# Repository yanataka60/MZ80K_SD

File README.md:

# MZ-80シリーズにSD-Cardとのロード、セーブ機能を

　ROMをF000Hに置くことでMZ-80シリーズにフロッピーディスク装置を外付けした際に起動するためのFDコマンドを利用できますが、フロッピーディスク装置の代わりにSD-CARDを繋いでしまおうというものです。

#### 　2025.7.31追記 MZ-80K、MZ-80K2、MZ-80K2E、MZ-80C、MZ-1200、MZ-700で動作しますが、MZ-700はRAMとの切替動作をサポートしたMZ-700_SDもあります。

　アダプタを繋ぐだけでもBASIC SP-5030が約4秒で起動できるようになるなどアプリケーションランチャーとして便利に使えますが、MONITOR SP-1002にパッチをあてることでBASIC SP-5030はもちろん、ほとんどのMZ-80KアプリケーションがSD-CARD対応となります。

### 本体ROMをパッチを当てたMONITOR SP-1002に交換しなくてもアプリケーションからのロード、セーブをSD対応とさせるパッチあてWindows用ツール「CMT2SD_CHECK」を公開しました。(2022.6.29)
### 詳細は、CMT2SD_CHECKフォルダ中のREADME.mdを参照してください。

　MZ-700もMZ-80K用アプリケーションについては同様にSD-CARD対応となりますが、標準添付のS-BASIC、Hu-BASICともMONITOR 1Z-009A、1Z-009BのCMTルーチンを利用していないためMONITOR 1Z-009A、1Z-009BにパッチをあてただけではSD-CARD対応となりません。

　S-BASICについてはパッチを当てることでSD-CARD対応となりますが、Hu-BASICは未対応です。

　基本的にはMZ-700ではMZ-80K互換機として利用できると考えてください。

　また、MZ-700もFDxコマンドは機能しますのでMZ-700用アプリケーションランチャーとして使えますが、MZ-80K対応とうたっていない64KオールRAMを前提としているMZ-700用アプリケーションはロードできない可能性があります。

　MZ-700+MZ-80K_SDでMZ-700用アプリケーションを実行したときにMZ-80K_SDのROMとMZ-700本体のRAMが衝突しないよう「ROM切り離しスイッチ」を取り入れましたが、これを自動で行うMZ-700_SD基板も公開しています。ただし、MZ-700_SDを作成するにはGAL16V8の入手が必要です。

　なお、一部のMZ-80K用ソフトはMZ-700で実行するにあたって、0h!MZ別冊 ADVANCED MZ-700に掲載されているSP-1002のMZ-700対応版 NZ-700が必要となるものがあります。

https://github.com/yanataka60/MZ-700_SD

#### 注）

　一応安定動作を確認していますが、SAVE動作によりSD-CARDに保存されたデータファイルの消失等考えられますのでファイルのバックアップをお願いします。

　Arduino、ROMへ書き込むための機器が別途必要となります。

### (2026.8.13追記)すねいるさんのBARYONに対応するためArduinoプログラムを更新しました。また、ROMプログラムも合わせて更新することで多段ロードにも対応します。

### 多段ロードの詳細については後述「BARYON対応」「多段ロード対応」を参照してください。

BARYON対応:https://github.com/yanataka60/MZ80K_SD#baryon%E5%AF%BE%E5%BF%9C2026813

多段ロード対応:https://github.com/yanataka60/MZ80K_SD#%E5%A4%9A%E6%AE%B5%E3%83%AD%E3%83%BC%E3%83%89%E5%AF%BE%E5%BF%9C2026813

## 回路図
　KiCadフォルダ内のMZ80K_SD.pdf参照

[回路図](https://github.com/yanataka60/MZ80K_SD/blob/main/KiCad/MZ80k_SD/MZ80K_SD.pdf)

## 部品
|番号|品名|数量|備考|
| ------------ | ------------ | ------------ | ------------ |
|U1|74LS04|1||
|U2|2764又は28C64|1|ROMの相性については後述|
|U3|8255|1||
|U4|Arduino_Pro_Mini_5V|1|Atmega328版を使用 168版は不可。(注1)|
|U5 U6|74LS30|2||
||J2、J5のいづれか|||
|J2|Micro SD Card Kit又は同等品|1|秋月電子通商 AE-microSD-LLCNV (注2) (注3)|
|J5|MicroSD Card Adapter|1|Arduino等に使われる5V電源に対応したもの (注3)|
|C1-C5|積層セラミックコンデンサ 0.1uF|5||
|C6|電解コンデンサ 16v100uF|1||
|S1 S2|3Pスライドスイッチ|2|秋月電子通商 SS12D01G4など|
|S3|3Pスライドスイッチ|1|MZ-700で使わなければ80K側固定のジャンパでも可|
|R1|カーボン抵抗 10kΩ|1|S3を使わずに80K側固定でジャンパするなら不要|
|J4|DCジャック|1||
|J3|コネクタ 2Pin|1|ピンヘッダで代用するときはGNDと間違えないよう1Pinで5Vだけにしたほうが良い|
|J1|50Pinコネクタ|1||
||50Pinケーブル|1||
||ピンヘッダ|2Pin分|Arduino_Pro_MiniにはA4、A5用のピンヘッダが付いていないため別途調達が必要です 秋月電子通商 PH-1x40SGなど|
||本体内から5Vを取る場合、ケーブル少々|||
||本体ROMにパッチをあてる場合、27C32等を2532ソケットに差すためのアダプタ|||
||ピンソケット(任意)|26Pin分|Arduino_Pro_Miniを取り外し可能としたい場合に調達します 秋月電子通商 FHU-1x42SGなど|

　　　注1)Arduino Pro MiniはA4、A5ピンも使っています。

　　　注2)秋月電子通商　AE-microSD-LLCNVのJ1ジャンパはショートしてください。

　　　注3)J2又はJ5のどちらかを選択して取り付けてください。

### MicroSD Card Adapterを使う
J5に取り付けます。

MicroSD Card Adapterについているピンヘッダを除去してハンダ付けするのが一番確実ですが、J5の穴にMicroSD Card Adapterをぴったりと押しつけ、裏から多めにハンダを流し込むことでハンダ付けをする方法もあります。なお、この方法の時にはしっかりハンダ付けが出来たかテスターで導通を確認しておいた方が安心です。

ハンダ付けに自信のない方はJ2の秋月電子通商　AE-microSD-LLCNVをお使いください。AE-microSD-LLCNVならパワーLED、アクセスLEDが付いています。

.JPG)

.JPG)

.JPG)

.JPG)

## ROMプログラムについて
　Z80フォルダ内にFD_rom1.bin、FD_rom2.bin、FD_rom.binと3つありますが、SD-CARDを利用するためのプログラムFD_rom1.bin(28C64の下位に配置)、MONITORをCMT利用に戻すためのプログラムFD_rom2.bin(28C64の上位に配置)、2つを合わせたプログラムFD_rom.binとなっています。

　ROMライター(TL866II Plus等)を使って2764又は28C64にFD_rom.binを書き込んでください。

　28C64にFD_rom.binを書き込むことでスライドスイッチによりSDとCMTを切り替えられるようにしてあります。

　ただし、稼働中に切り替えるとタイミングによってはMZ-80Kが暴走する時があります。基本的には電源を切って切り替えてください。

　また、FD_rom2の領域には4023Byte分の空きエリアがあります。自由に使っていただいて構いません。

　なお、MZ-700でMONITOR 1Z-009A、1Z-009BにMZ-80K_SD用のパッチをあてた状態でもCMT側に切り替えれば紅茶羊羹さんの「MZ⇔PC間でデータを転送する（USB版）」が問題なく使用できます。

## ROMの相性
　すべての状況をテストできたわけではないのですが、ROMの個体によっては相性があるのではないかとの報告があります。

　特に問題なく動いているROMと動かない個体の例が報告されているROMを以下に列挙します。

　これからROMを調達される方はなるべく「特に問題なく動いているROM」を調達したほうが無難だと思われます。

|特に問題なく動いているROM|
| ----------------------- |
|AT28C64B                 |
|CAT28C64BP               |
|M2764A                   |

|動かない個体の例が報告されているROM|
| --------------------------------- |
|HN484764G                          |
|M27C64A                            |
|TMM2764D                           |
|TMS2764                            |
|D28C64ACZ                          |

## Arduinoプログラム
　Arduino IDEを使ってArduinoフォルダ内のMZ-80K_SD.inoを書き込みます。

　SdFatライブラリを使用していますのでArduino IDEメニューのライブラリの管理からライブラリマネージャを立ち上げて「SdFat」をインストールしてください。

　「SdFat」で検索すれば見つかります。「SdFat」と「SdFat - Adafruit Fork」が見つかりますが「SdFat」のほうを使っています。

注)Arduinoを基板に直付けしている場合、Arduinoプログラムを書き込むときは、MZ-80K本体とは接続を外し、74LS04を外したうえで書き込んでください。

## MZ-80Kとの接続
　回路図J1のピン番号とMZ-80K外部拡張端子のピン番号は一致していません。ピン配置は一致していますのでJPGフォルダにある「Rev1.5.1+MZ-80K Series(6).JPG」を参考にフラットケーブルで接続してください。

　MZ-700の外部拡張端子はMZ-80Kとピン配置は同じですが、ピンコネクタではなく、カードエッジコネクタです。

.JPG)

.JPG)

.JPG)

## 電源
　MZ-80Kのバスには+5Vが出ていないため、最初はDCジャックから外部電源を供給するつもりだったのですが、本体と電源が一緒のほうが扱いが楽そうだったので本体から+5Vを引き出して供給する用のコネクタと二通りを用意しています。

　MZ-80K内部から5Vを取得するには、27C32等を2532ソケットに差すためのアダプタから引っ張ってくるのが簡単だと思います。

## MONITOR ROMの差し替え
　MONITOR SP-1002、MONITOR 1Z-009A、1Z-009Bとも以下のパッチをあててください。

　0437 : D5 → C3

　0438 : C5 → 04

　0439 : E5 → F0

　0476 : D5 → C3

　0477 : C5 → 07

　0478 : E5 → F0

　04D9 : D5 → C3

　04DA : C5 → 0A

　04DB : E5 → F0

　04F9 : D5 → C3

　04FA : C5 → 0D

　04FB : E5 → F0

　0589 : D5 → C3

　058A : C5 → 10

　058B : E5 → F0

　MZ-700 MONITOR 1Z-009A、1Z-009Bについては、RAMにコピーしたMONITORにパッチを当てることでパッチを当てたROMに差し替えなくても済むように「FT.MZT」を作成しました。

　「FT.MZT」をSD-CARDのルートに置き、FD FT[CR]を実行することでRAM MONITORに制御が移ります。

　「FT.MZT」と同等の動作をするFDZコマンドを新設しました。FDZコマンドを使えば「FT.MZT」は必要ありません。

　また、紅茶羊羹さんの「MZ⇔PC間でデータを転送する（USB版）」でMZTrans用パッチをMONITOR 1Z-009A、1Z-009Bに当てているとFコマンドが使えないので以下のパッチを当てることで'#'コマンドをつぶして'F'コマンドを復活させます。

　00D2 : 23 → 46

　00D4 : 86 → 21

　紅茶羊羹さん作成の「TR.MZT」をSD-CARDのルートに置き、「FD TR」を実行することでMZTransを使う方法もあります。

## BASIC SP-5030 バージョン違い

　BASIC SP-5030には、旧・新・VER1.0Aの３種類のバージョンがあるそうで、そのうち新・VER1.0Aの二つはパッチをあてる必要があります。以下のアドレスが4049H、4069Hを指している場合には新・VER1.0Aのどちらかですので以下のように修正する必要があります。

アドレスはMZTファイルのアドレスです。実アドレスは()内

　18C5(1845) : 49 → 27

　18C6(1846) : 40 → 00

　1939(18B9) : 69 → 2A

　193A(18BA) : 40 → 00

　19EA(196A) : 69 → 2A

　19EB(196B) : 40 → 00

　1AE0(1A60) : 69 → 2A

　1AE1(1A60) : 40 → 00

## SD-CARD
　出来れば8GB以下のSDカードを用意してください。

　ArduinoのSdFatライブラリは、SD規格(最大2GB)、SDHC規格(2GB～32GB)に対応していますが、SDXC規格(32GB～2TB)には対応していません。

　また、SDHC規格のSDカードであっても32GB、16GBは相性により動作しないものがあるようです。

　FAT16又はFAT32が認識できます。NTFSは認識できません。

　ルートに置かれたMZTファイルのみ認識できます。(MZT以外のファイル、フォルダも表示されますがLOAD実行の対象になりません)

　ファイル名は「.MZT」を除いて32文字まで、ただし半角カタカナ、及び一部の記号はArduinoが認識しないので使えません。パソコンでファイル名を付けるときはアルファベット、数字および空白でファイル名をつけてください。

## 操作方法
　MONITORコマンド入力待ちから以下のコマンドが利用できます。

　なお、MZ-700のフロッピーディスク装置起動コマンドは本来'F'の一文字ですが、操作方法としては'FD'に統一しました。

　以下、SD-CARD内のファイルに付けられるファイル名をDOSファイル名、MZT形式ファイルのインフォメーションブロック内ファイル名をIBFファイル名とします。

### FD[CR]
　FDのみでDOSファイル名「0000.MZT」がLOAD及び実行されます。

　「0000.MZT」は、パソコンでBASIC SP-5030等をリネームコピーして作成しても大丈夫ですが、FDAコマンドから作ることもできます。

### FD　DOSファイル名[CR]
　DOSファイル名で指定したバイナリファイルをLOADして実行します。

　「.MZT」は省略可能です。

　MONITORのLOADコマンドの代替として使えます。なお、LOADコマンドも使えますが、アプリケーションからのLOADと同じ扱いになります。

例)

FD　TEST[CR]

### FD/DOSファイル名[CR] 又は FD/　DOSファイル名[CR]
　DOSファイル名で指定したバイナリファイルをLOADします。実行はしません。

　「.MZT」は省略可能です。

例)

FD/TEST[CR]

FD/　TEST[CR]

### FDL[CR]
　SD-CARDルートディレクトリにあるファイルの一覧を表示します。20件表示したところで指示待ちになるので打ち切るならSHIFT+BREAK又は↑を入力すると打ち切られ、Bキーで前の20件に戻ります。それ以外のキーで次の20件を表示します。

　行頭に「*FD」を付加して表示してあるので実行したいファイルにカーソルキーを合わせて[CR]キーを押すだけでLOAD、実行が可能です。

　表示される順番は、登録順となりファイル名アルファベッド順などのソートした順で表示することはできません。

### FDL　x[CR]
ファイル名がxで始まるファイルの一覧を表示します。20件表示したところで指示待ちになるので打ち切るならSHIFT+BREAK又は↑を入力すると打ち切られ、Bキーで前の20件に戻ります。それ以外のキーで次の20件を表示します。

xはMZのキーボードから入力可能な32文字までの文字列です。(数字、記号、アルファベット)

例)

FDL S[CR]

FDL SP[CR]

FDL BASIC S[CR]

### FDA　DOSファイル名[CR]
　DOSファイル名で指定したファイルを「0000.MZT」という名前でリネームコピーします。

　FDLコマンドで表示されたファイル名をカーソルで選択し、行頭の「*FD」に「A」だけ付加して[CR]キーを押せば簡単です。

### FDS　SAVE開始アドレス　SAVE終了アドレス　実行開始アドレス　DOSファイル名[CR]
　SAVE開始アドレスからSAVE終了アドレスまでをDOSファイル名でSAVEします。

　SAVE開始アドレス、SAVE終了アドレス、実行開始アドレスは16進数4桁で指定します。DOSファイル名の「.MZT」は省略可能です。

例)

FDS　1200　2FFF　1200　TEST[CR]

### FDC　DOSファイル名[CR]
　DOSファイル名で指定したファイルをコピーします。

　FDLコマンドで表示されたファイル名をカーソルで選択し、行頭の「*FD」に「C」だけ付加して[CR]キーを押せば簡単です。

　DOSファイル名を入力し、[CR]キーを押すと「NEW NAME:」と聞いてくるので新しいDOSファイル名を入力して[CR]キーを押します。

　新しいDOSファイル名に既にあるDOSファイル名を指定するとコピーせずに中断します。

例)

FDC　TEST[CR]

NEW NAME:TEST2[CR]

### FDR　DOSファイル名[CR]
　DOSファイル名で指定したファイルをリネームします。

　FDLコマンドで表示されたファイル名をカーソルで選択し、行頭の「*FD」に「R」だけ付加して[CR]キーを押せば簡単です。

　DOSファイル名を入力し、[CR]キーを押すと「NEW NAME:」と聞いてくるので新しいDOSファイル名を入力して[CR]キーを押します。

　新しいDOSファイル名に既にあるDOSファイル名を指定するとリネームせずに中断します。

例)

FDR　TEST[CR]

NEW NAME:TEST2[CR]

### FDD　DOSファイル名[CR]
　DOSファイル名で指定したファイルを削除します。

　FDLコマンドで表示されたファイル名をカーソルで選択し、行頭の「*FD」に「D」だけ付加して[CR]キーを押せば簡単です。

　DOSファイル名を入力し、[CR]キーを押すと「FILE DELETE?(Y:OK ELSE:CANSEL)」と聞いてくるのでYを押せば削除されます。Y以外のキーを押すとキャンセルとなります。

### FDP　DOSファイル名[CR]
　DOSファイル名で指定したファイルの内容をDUMPします。

　FDLコマンドで表示されたファイル名をカーソルで選択し、行頭の「*FD」に「P」だけ付加して[CR]キーを押せば簡単です。

　DOSファイル名を入力し、[CR]キーを押すとファイルの内容を128Byteを一画面として表示します。

　一画面表示したところで「NEXT:ANY BACK:B BREAK:SHIFT+BREAK」と表示して指示待ちとなるのでBで前の128Byteを表示、SHIFT+BREAKで中止、それ以外のキーで次の128Byteの表示となります。

　ファイルサイズが128Byteで割り切れない場合には最後のページは128Byteに揃うまで00Hで埋められます。

　ファイル内容を書き換えることはできません。

### FDM　開始アドレス[CR]
　開始アドレスからMZ-80Kのメモリ内容を128Byteを一画面として表示します。

　一画面表示したところで「NEXT:ANY BACK:B BREAK:SHIFT+BREAK」と表示して指示待ちとなるのでBで前の128Byteを表示、SHIFT+BREAKで中止、それ以外のキーで次の128Byteの表示となります。

　一画面表示している途中でもSHIFT+BREAKでいつでも中止できます。

### FDW　開始アドレス　1Byte(16進2桁)データ[CR]
　開始アドレスから16進2桁データをMZ-80Kのメモリに書き込みます。

　開始アドレスに続けて16進2桁で書き込むデータを記述し[CR]キーを押します。データの区切りの空白は無視しますのであってもなくても構いません。

　16進2桁のByteデータは一行に収まる範囲なら何Byte分を続けても構いません。

　一行入力して[CR]キーを押すとデータが書き込まれ、次のアドレスが表示されるので続けてデータを入力していけます。

　また、アドレスを修正すれば戻って修正や離れたアドレスにデータを書き込むことも可能です。

　データの書き込みを止めるときは表示されたアドレスにデータを書かずに[CR]キーを押します。

　16進数以外を入力して[CR]キーを押した場合には16進数以外を入力した直前までの有効なデータを書き込み次のアドレスを表示します。

例)

*FDW　1200　01　02　03　04　05　06　07　08[CR]

*FDW　1200　0102030405060708[CR]

*FDW　1200[CR]　(止めるとき)

*FDW　1200　12　34　5/[CR]　(12　34まで書き込まれます)

### FDZ[CR]
　【MZ-700専用】MZ-700用に作成した「FT.MZT」と同等の動きをします。 MONITOR 1Z-009A又は1Z-009Bを裏RAMにコピーしたうえでパッチを当てた後、裏RAM上のMONITORがスタートします。

　MZ-80Kで実行してしまった場合には、RESET動作となります。

### FDU[CR]
　【MZ-700専用、裏RAM MONITORで運用中にRESETした場合に限る】裏RAMに切り替え裏RAMのMONITORをスタートさせます。

　注）裏RAMにMONITORが無い状態で実行すると暴走します。

　MZ-80Kで実行してしまった場合には、RESET動作となります。

### アプリケーションからのLOAD
　L、LOAD等アプリケーションが指定したコマンドの後ろにはIBFファイル名を指定可となっていますが、指定せずにL、LOAD等のコマンドのみで[CR]キーを押します。

　CMTの場合にはここでPLAYボタンを押すよう指示が出るところですが、「DOS FILE:」と表示して行入力待ちになっていますのでDOSファイル名を入力して[CR]キーを押します。この時、「.MZT」の入力は省略できます。

　DOSファイル名は「.MZT」を除いて32文字まで、ただし半角カタカナ、及び一部の記号はArduinoが認識しないので使えません。パソコンでファイル名を付けるときはアルファベット、数字および空白でファイル名をつけてください。

例)BASIC SP-5030では

× LOAD "TEST"[CR]

○ LOAD[CR]

　DOS FILE:TEST[CR]

○ LOAD[CR]

　DOS FILE:TEST.MZT[CR]

** 参考 **

　S-OS SWORDでの運用に当たっては起動直後に「DV S:」としてデバイスを各SYSTEMデバイスとしてください。

　FUZZY BASICだけかもしれませんが共通フォーマットデバイスのままだとLOADコマンドでIBFファイル名の省略ができませんでした。

#### LOAD時の特殊コマンド
　「DOS FILE:」と表示して行入力待ちになったときに以下の特殊コマンドが使用可能です。

##### *FDL[CR]
##### *FDL x[CR]
　MONITORコマンド入力待ちからのFDL、FDL xと全く同等のファイル一覧機能が使えます。

　検索結果の行頭には「DOS FILE:」を付加して表示してあるのでLOADしたいファイルにカーソルキーを合わせて[CR]キーを押すだけでLOADが可能です。

　「*FDL」で検索、カーソルで選んで読み込もうとした場合に「DOS FILE:」に戻ってしまうアプリケーションがありますが、再度カーソルを合わせて[CR]すれば読み込めます。

### アプリケーションからのSAVE
　CMTの時と同様にアプリケーションの指定する入力方法、ルールでファイル名等を入力して保存してください。

　ただし、半角カタカナはArduinoが認識できないため、使用できません。アルファベット、数字および空白で指定してください。

　SAVE時は、入力したファイル名がIBFファイル名、DOSファイル名の両方に適用されます。

　DOSファイル名としての「.MZT」は自動的に付加されます。

例)BASIC SP-5030では

○ SAVE "TEST"[CR]

## 操作上の注意
　~~「SD-CARD INITIALIZE ERROR」と表示されたときは、SD-CARDをいったん抜き再挿入したうえでArduinoをリセットしてください。~~

　~~SD-CARDにアクセスしていない時に電源が入ったままで SD-CARDを抜いた後、再挿入しSD-CARDにアクセスすると「SD-CARD INITIALIZE ERROR」となる場合があります。再挿入した場合にはSD-CARDにアクセスする前にArduinoを必ずリセットしてください。~~

　~~SD-CARDの抜き差しは電源を切った状態で行うほうがより確実です。~~

　(2024.3.10) SD-CARDにアクセスしていない時に電源が入ったままでSD-CARDを抜くと再度SD-CARDを挿入してもSD-CARDにアクセスできない問題を解消しました。(Arduinoを最新版に書き換えてください)

　再度SD-CARDを挿入した後、FDL、LOAD、SAVE等でSD-CARDに3回ほどアクセスすれば復旧します。

　SD-CARDへのセーブ時にDOSファイル名を指定せずに[CR]を押下してしまった場合、「.MZT」というDOSファイルが作成されてしまいます。この「.MZT」はアプリケーションからLOADする時にDOSファイル名を指定せずに[CR]を押下した場合に読み込まれることで不測の動作を起こす原因になりますので作成された場合には削除しておく方が無難です。

　なお、「.MZT」は現在FDR及びFDDコマンドでは認識できませんので、Windowsパソコンから消去してください。

## SD-CARDに読み書きできるかを試した結果

　読み書き出来たもの(アルファベット順)

　　BASE-80 Ver35【I/O 1981年4月号】

　　BASIC SP-5030(パッチあて必要なバージョンあり)

　　CAP-Xインタプリタ【I/O 1980年5月号】

　　EDASM V1.2B【Oh!MZ 1985年1月号】

　　FORM VER1.0(注3)【I/O 1980年6月号】

　　FORTRAN-MZ V.1【I/O 1981年1月号】

　　GAME-MZ80K V.1(注1)【ASCII 1979年10月号】

　　HU-BASIC V1.3

　　KM-BASIC ver 0.8.3-beta(注2)

　　LSIアセンブラ(注1)【【ASCII 1979年11月号】

　　M-FORTH/MZ V1.1(注1)【I/O 1981年3月号】

　　micro PASCAL-MZ VER 2.2【ASCII 1980年6月号】

　　MONIOS【月刊マイコン 1982年2月号】

　　PALL【I/O 1979年12月号】

　　S-OS SWORD(S-OS用アプリ含む)【Oh!MZ 1986年2月号】【再掲載 Oh!MZ 1987年3月号】

　　SELF RELOCATABLE DEBUGGER【I/O 1980年11月号】

　　SP-2101 Z80 ASSEMBLER

　　SP-2201 TEXT EDITOR

　　SP-2301 RELOCATE LOADER

　　SP-2401 SYMB DEBUGGER

　　TL/1(注1)(注3)【ASCII 1981年5月号】

　　TTL VERSION 1.1【Oh!MZ 1984年10月号】

　　WICS INTERPRETER VER 1.1(注3)【I/O 1981年10月号】

　　8080用テキスト・エディタ＆アセンブラ【I/O 1980年9月号】

　　マシン語モニタ【I/O 1979年10月号】【I/O合本 MZ-80活用研究】

　　整数型ベーシックコンパイラー for MZ-80K/C, MZ-1200(注1)(注3)【諏訪工房】

注1)このアプリケーションはMZ-700非対応です。MZ-700で動かすには、0h!MZ別冊 ADVANCED MZ-700に掲載されているSP-1002のMZ-700対応版 NZ-700が必要です。NZ-700にSP-1002と同じようにMZ-80K_SDのパッチをあてることでMZ-700でも同様にLOAD、SAVEが可能となります。

注2)SAVEコマンドでファイルネームは指定できないようです。SAVE[CR]で「KMB-FILE VER 1.0」のファイルネームで保存されました。

注3)LOADコマンドから「*FDL」で検索、カーソルで選んで読み込もうとした場合に「DOS FILE:」に戻ってしまいますが、再度カーソルを合わせて[CR]すれば読み込めます。

　読み書き出来なかったもの

　　EDAS FOR MZ-1200 VER 1.2【I/O 1982年11月号】

　　EXIT MONITOR【ASCII 1981年6月号】

## MZ700用プログラムで起動確認したもの
　　S-BASIC 1Z-007B(LOAD、SAVEもSD対応となるパッチを公開しました)

　　S-OS SWORD(MZ-700用SWORDでSD-CARD運用するにはMONITOR-ROMの書き換えが必要です。MONITOR-ROMを書き換えずに「FT.MZT」又はFDZコマンドを実行しても起動後のLOAD、SAVEはCMTとなります)

　　HUBASIC VERSION 2.0A(起動後のLOAD、SAVEはCMT)

　　tiny XEVIOUS mz-700

　　タイムシークレット(すべてのプログラムを別ファイルとして保存が必要)

　　タイムトンネル(すべてのプログラムを別ファイルとして保存が必要)

　　TS-700(「I/O別冊 WICS・BASEプログラム集」掲載、TS-700フォルダ参照)

　　SuperBASE-700(「I/O別冊 WICS・BASEプログラム集」掲載、TS-700フォルダ参照)

　　WICSインタプリタ、コンパイラ(「I/O別冊 WICS・BASEプログラム集」掲載、TS-700フォルダ参照)

なお、起動確認していないアプリケーションでも起動だけであればFDコマンドで起動できる可能性があります。

## 自作アプリケーションでMZ-80K_SDからLOADするDOSファイル名を指定したい場合
　MZ-80K用自作アプリケーションでMZ-80K_SDからデータ・機械語プログラム等のバイナリデータをLOADする処理を追加したい場合にはF00Ah(MLHED)をコールしてDOSファイル名を入力した後、F00Dh(MLDAT)をコールしてデータをロードとなり、DOSファイル名をアプリケーションの中で指定しておくことが出来ません。

　そこで以下の機械語をアプリケーションに組み込み、コールすることでアプリケーション内でDOSファイル名を指定することが可能です。

　その後、F00DHをコールすればSDからLOADが実行されます。

|コード|
| ------------ |
|MLHED:　　LD　　　DE,FNAME|
|　　　　　DI|
|　　　　　PUSH　　DE|
|　　　　　PUSH　　BC|
|　　　　　PUSH　　HL|
|　　　　　CALL　　F082H|
|　　　　　PUSH　　DE|
|　　　　　XOR　　　A|
|　　　　　LD　　　DE,0000H|
|　　　　　CALL　　0033H|
|　　　　　POP　　　DE|
|　　　　　JP　　　F85BH|
|FNAME:|
|　　　　　DB　　　'TEST',0DH|

#### BASIC SP-5030のプログラム中でMZ-80K_SDからLOADするDOSファイル名を指定したい場合
　BASIC SP-5030で使うときは以下の機械語を適当なアドレスに配置し、BASICから呼び出します。

　わずかな機械語ですのでBASICプログラム中にDATA文にしておき、LIMIT文で機械語領域を確保、READ文で読み込み、POKE文でメモリに書き込むようにすれば手軽です。

|コード|
| ------------ |
|MLHED:　　DI|
|　　　　　PUSH　　DE|
|　　　　　PUSH　　BC|
|　　　　　PUSH　　HL|
|　　　　　CALL　　F082H|
|　　　　　PUSH　　DE|
|　　　　　XOR　　　A|
|　　　　　LD　　　DE,0000H|
|　　　　　CALL　　0033H|
|　　　　　POP　　　DE|
|　　　　　JP　　　F85BH|

DATA 243,213,197,229,205,130,240,213,175,017,000,000,205,051,000,209

DATA 195,091,248

##### BASIC SP-5030からの呼び出し

|コード|備考|
| ------------ | ------------ |
|G＄="TEST"|DOSファイル名を表す文字列を文字列変数に代入|
|USR(＄C000,G＄)|機械語を配置したアドレスとDOSファイル名を表す文字列を代入した文字列変数を値としてUSR関数を実行(SP-5030の場合文字列関数に代入された文字列の最後に0Dhが入ってます)|
|USR(＄F00D)|SDからデータをLOAD|

#### MZ-700でDOSファイル名を指定したい場合
　MONITOR 1Z-009A(B)上で動くアプリケーションであればF000hからのROMにバンク切替(OUT (E3h),A)することを考慮すればMZ-80Kと同じように機械語をコールすることで指定できるようになるはずです。

　S-BASIC上でDOSファイル名を指定するにはバンク切替の他、文字列関数に代入された文字列の最後が00hで終わっていること、インフォメーションブロック(IFB)の位置もMONITOR 1Z-009A(B)とは違う等の差異を解決できる方以外はハードルが高いかもしれません。

## 専用トレイ
　カセット部に被せて使うMZ-80K_SD用トレイを公開しました。

https://yanataka.booth.pm/items/6058283

　MZ-1200用はこちらです。

https://yanataka.booth.pm/items/6069703

## BARYON対応(2026.8.13)
　MZ-700本体ROMにMZ-80K_SD(MZ-700_SD)用パッチを当てていなければBARYONの3分割mztファイル(baryon-1.mzt,baryon-2.mzt,baryon-3.mzt)で問題なく起動しますが、MZ-700本体ROMにMZ-80K_SD(MZ-700_SD)用パッチを当てていると異常動作により起動できません。

　これに対応するため、Arduinoプログラムを更新しましたので書き換えてください。

　これによりBARYON 3分割mztファイル(baryon-1.mzt,baryon-2.mzt,baryon-3.mzt)が正常に起動するようになります。

　また3つのmztファイルを連結したものとして提供されているbaryon.mztを「baryon$.mzt」とファイルネームの最後に「$」を付けることで起動できるようになりました。

## 多段ロード対応(2026.8.13)
　Arduino、ROMの両方を更新することで次の４種類の多段ロードに対応します。

　ただし、IPL.ROM内のCMTサービスルーチンをコールしていることが条件です。２段目以降のLOADにサービスルーチンをコールせず、独自プログラムで読み込むプログラムには対応できません。

### ①複数mztファイル連続読み込み
　連続して読み込ませたいmztファイルのファイル名の最後に#n(n=1～9)連続する数字を付加します。

例)

hoge#1.mzt

hoge#2.mzt

hoge#3.mzt

### ②連結mzt
　連続して読み込ませたいmztファイルを単純にマージしたmztファイルです。ファイル名の最後に#を付加してください。

例)

hoge#.mzt

### ③連続データブロック形式(IFB、DATA、DATA…)[ダミーヘッダ無]
　インフォーメションブロックに続き、複数のデータブロックが配置されたmztファイルです。実機CMTファイルで多段ロードに使用されることがある形式でダミーヘッダはありません。ファイル名に制限はありません。

例)

hoge.mzt

### ④連続データブロック形式(IFB、DATA、(IFB)、DATA…)[ダミーヘッダ有]
　インフォーメションブロックに続き、複数のデータブロックが配置されたmztファイルです。③の形式ですが、IFBがないと動作しないエミュレータ用にダミーヘッダが付加されたものです。③と区別するためにファイル名の最後に$を付加してください。

例)

hoge$.mzt

## 謝辞
　基板の作成に当たり以下のデータを使わせていただきました。ありがとうございました。

　Arduino Pro Mini

　　https://github.com/g200kg/kicad-lib-arduino

　AE-microSD-LLCNV

　　https://github.com/kuninet/PC-8001-SD-8kRAM

　MZ-700への対応に当たっては、紅茶羊羹様の「MZ⇔PC間でデータを転送する（USB版）」が非常に参考になりました。ありがとうございました。

　不安定動作の解消に以下の皆様にご協力とご助言をいただきました。ありがとうございました。(アルファベット順)

　　EIJ様

　　hlide fremen様

　　junk_suga様

　　retrogamer128様

　Arduino等に使われる5V電源に対応したMicroSD Card Adapterを使って作られた事例をご報告いただきました。ありがとうございました。

　　𝕊𝕖ñ𝕠𝕣 𝔼𝕤𝕥𝕖𝕓𝕒𝕟様

## 追記
2021.12.12

　MZ-700をMZ-80Kの代わりとして使うだけならNZ-700を最初に起動すればパッチを当てたROMを焼かなくてもいいんだと気づきました。FDコマンドでNZ-700が起動するようにすればMZ-700のほうがハードルが低いかもしれません。

2021.12.12

　MZ-700用に「FT.MZT」を作成しました。

2021.12.13

　KiCad\MZ80k_SDフォルダの回路図MZ80K_SD.pdfをRev1.1に更新

2021.12.13

　MZ-80KのS-OS SWORDでアプリケーションをLOADしようとしたとき、最初の一回だけはなぜかインフォメーションブロックの読み込みで止まってしまい、継続するためにはキーを一回押す必要がある原因は、FLGETのDEBUGにMZ-700用の修正もしてしまっていたせいでした。元に戻したところ無事解消。

2021.12.14

　S-BASICについてSD-CARD対応とするパッチを公開しました。

2021.12.18 2021.12.19 2021.12.21

　(MZ-80Kの電源状況によっては内部電源では動作不安定になることもあるようです。不安定な挙動がある場合には外部電源を試してください。)

　昨日追記した挙動不安定は電源のせいではなく、28C64がハズレあるいは個体差によりブラウン管の磁気の影響を受けていたためでした。

　28C64に個体差があるとは思われますが、それを吸収すべきプログラムにバグがあったので修正。

2021.12.20

　27C64に対応するためROMの1PinをVCCに接続し、基板をRev1.2としました。

2021.12.24

　安定性向上のためプルアップ抵抗を追加することにしました。回路図、基板データの検証が終わり次第公開を予定しています。また、エラー処理にバグがありましたのでこちらもテストが終わり次第公開したいと思います。

2021.12.26

　エラー処理のバグを修正。回路修正は後日。

2021.12.29

　MZ-700 MONITOR 1Z-009Aを入手し動作に支障がないことを確認しました。

2022.1.19

　GALが不安定動作の原因と思われるため、TTLで置き換えました。テスト環境では今のところ非常に安定しています。

　今まで不安定動作の要因と思われていた内部電源、外部電源、28C64の個体差、ブラウン管の磁気の影響、プルアップ抵抗等についてもTTLに置き換えたことで解消されています。

2022.1.23

　04D8H MONITOR リード インフォメーション代替処理のバグを修正。HU-BASIC V1.3、8080用テキスト・エディタ＆アセンブラのLOAD時に起こっていたエラーに対処。

2022.1.24

　SAVE時ファイルネームの後ろの空白に対処する処理をArduino側からMZ-80K側に変更。

　Arduinoの比較演算子の記述を見直し。

2022. 1.25

　0475H MONITOR ライト データ代替処理、04F8H MONITOR リード データ代替処理での8255初期化を廃止

　Arduino側での各コマンド受信時のdelay()を廃止

2022.1.26

　FDコマンドでロード可能なファイル種類コードは0x01のみとしていた制限を撤廃した

2022.1.28

　MZ-700用「FT.MZT」の動作をするFDZ、FDUコマンドを新設した。

2022.1.29

　特定環境下でLOAD、SAVEを行うとアプリケーションが固まってしまう原因のCMT代替処理RETURN時の割込み許可(EI)を削除。

　FDPコマンドで前ページに戻ると表示が乱れる場合がある症状を修正。

2022.1.30

　FDLコマンド仕様変更 FDL A～Zの場合、ファイル名先頭一文字を比較して一致したものだけを出力

2022.1.31

　FDLコマンド仕様変更 FDL nでのページ指定を廃止。FDL xでキーボードから入力可能なすべての文字で先頭一致とした。代わりにBキーで前の20件に戻れる機能を追加した。

　FDコマンド実行後アプリ動作が固まってしまう機械、アプリへの対処

2022.2.2

　DOSファイル名がアルファベット小文字でもFDL xで検索できるよう修正

2022.2.4

　ArduinoにMZ-1200対策

2022.2.9

　FDLコマンド仕様変更 FLD xの比較文字列を32文字以内とした。

2022.2.10

　ROMの相性について付記しました。

　アプリケーションのLOADコマンドの中でFDLコマンドが使える機能を実装しました。

2022.2.11

　アプリケーションのLOADコマンドの中でFDLコマンドが使える機能がMZ-700 MONITOR 1Z-009A、1Z-009B環境下では使えないバグを修正しました。

2022.2.15

　外部電源での起動に躓く場合の対処法を記載。

2022.2.26

　基板をRev1.5.2に更新。外部電源での稼働時において起動が躓く現象に対処。Rev1.5.1をRev1.5.2相当への改造方法を掲載。

2022.3.27

　基板のシルク印刷の向きを修正。

　アプリケーションからDOSファイル名を指定せずにSAVEしたときの挙動について追記。

2022.3.28

　誤字修正　誤「FDC及びFDDコマンド」 -> 正「FDR及びFDDコマンド」

2022.4.8

　Rev1.5.2基板でも機体によっては、電源ON時に起動に躓くことがあるようです。本体をリセットすることで解消できますが、気になる方はArduinoプログラム74行目の「delay(1000)」を「delay(1500)」ぐらいにしてみてください。

2022.4.24

　KiCad Libraryの定数を修正。

2022.5.31

　誤解を招く表現を修正

　修正前)DOSファイル名を指定せずに[CR]を押下してしまった場合、

　修正後)SD-CARDへのセーブ時にDOSファイル名を指定せずに[CR]を押下してしまった場合、

2022.6.29

　アプリケーションからのロード、セーブをSD対応とさせるパッチあてWindows用ツール「CMT2SD_CHECK」を公開しました。

　回路図にネットラベルを追加しました。

2022.6.30

　Z80フォルダの「FD_rom.BIN」を今回の「FD_rom.BIN」へ置き換えました。

　「CMT2SD_CHECK」によりパッチを当てたアプリケーションを使うときには新しい「FD_rom.BIN」への交換が必要です。

2022.8.4

　Arduinoを基板に直付けしている場合、Arduinoプログラムを書き込むときの注意点を書き加えました。

2022.9.11

　MicroSD Card Adapter用の端子を付加し、基板をRev1.5.3に更新。

2023.6.19

　MZ-2000_SDの起動方式追加によりArduinoプログラムを修正。MZ-80K_SDには影響なし。

2023.9.20

　「I/O別冊 WICS・BASEプログラム集」に掲載されているTS-700、SuperBASE-700、WICSインタプリタ、コンパイラへの対応を追加した。

2023.9.23

　Tookatoさんから報告のあった「D28C64ACZ」を動かない個体の例が報告されているROMのリストに追加しました。

2024.1.15

　SDカードは8GB以下が望ましいことを追記。

2024.3.4

　「自作アプリケーションでMZ-80K_SDからLOADするDOSファイル名を指定したい場合」を追記。

2024.3.10

　電源が入ったままでSD-CARDを抜くと再度SD-CARDを挿入してもSD-CARDにアクセスできない問題を解消した。

2024.7.29

　Tookato様作MZ-700用ロポコVersion 1.2.2をMZ-80K_SD対応とするパッチを公開しました。

2024.7.31

　MZ-700用ロポコVersion 1.2.2をMZ-80K_SD対応とするパッチをMZ-1500_SD共用にしました。

2024.8.2

　Tookato様からご指摘により、MZ-700+MZ-80K_SDでロポコを遊ぶとき、SDから起動後にS2スイッチをSDからCMTに切り替える必要があることを追記しました。

2024.8.8

　ROM切り離しスイッチの増設方法を追加しました。

2024.9.1

　専用トレイを公開しました。

2024.10.10

　ROM切り離しスイッチを標準装備としたRev1.5.5基板及び自動切り替えとしたMZ-700_SDの記述を加えました。

2025.7.31

　MZ-80シリーズでの動作について追記。

2025.12.4

　kuran_kuranさんにArduinoプログラムのバグを発見していただきました。精査した結果、不要な処理が含まれていることが原因であったため不要な処理部分を削除しました。なお、未修正のままでも実害はありません。kuran_kuranさん、ありがとうございました。

2026.8.13

　BARYONに対応しました。

　retrogamer128さんの要望により多段ロードに対応しました。

2026.8.15

　旧基板用の記述を整理しました。ロポコがMZ-80K_SD、MZ-700_SD、MZ-1500_SDに正式対応となっていますので関連の記述を削除しました。

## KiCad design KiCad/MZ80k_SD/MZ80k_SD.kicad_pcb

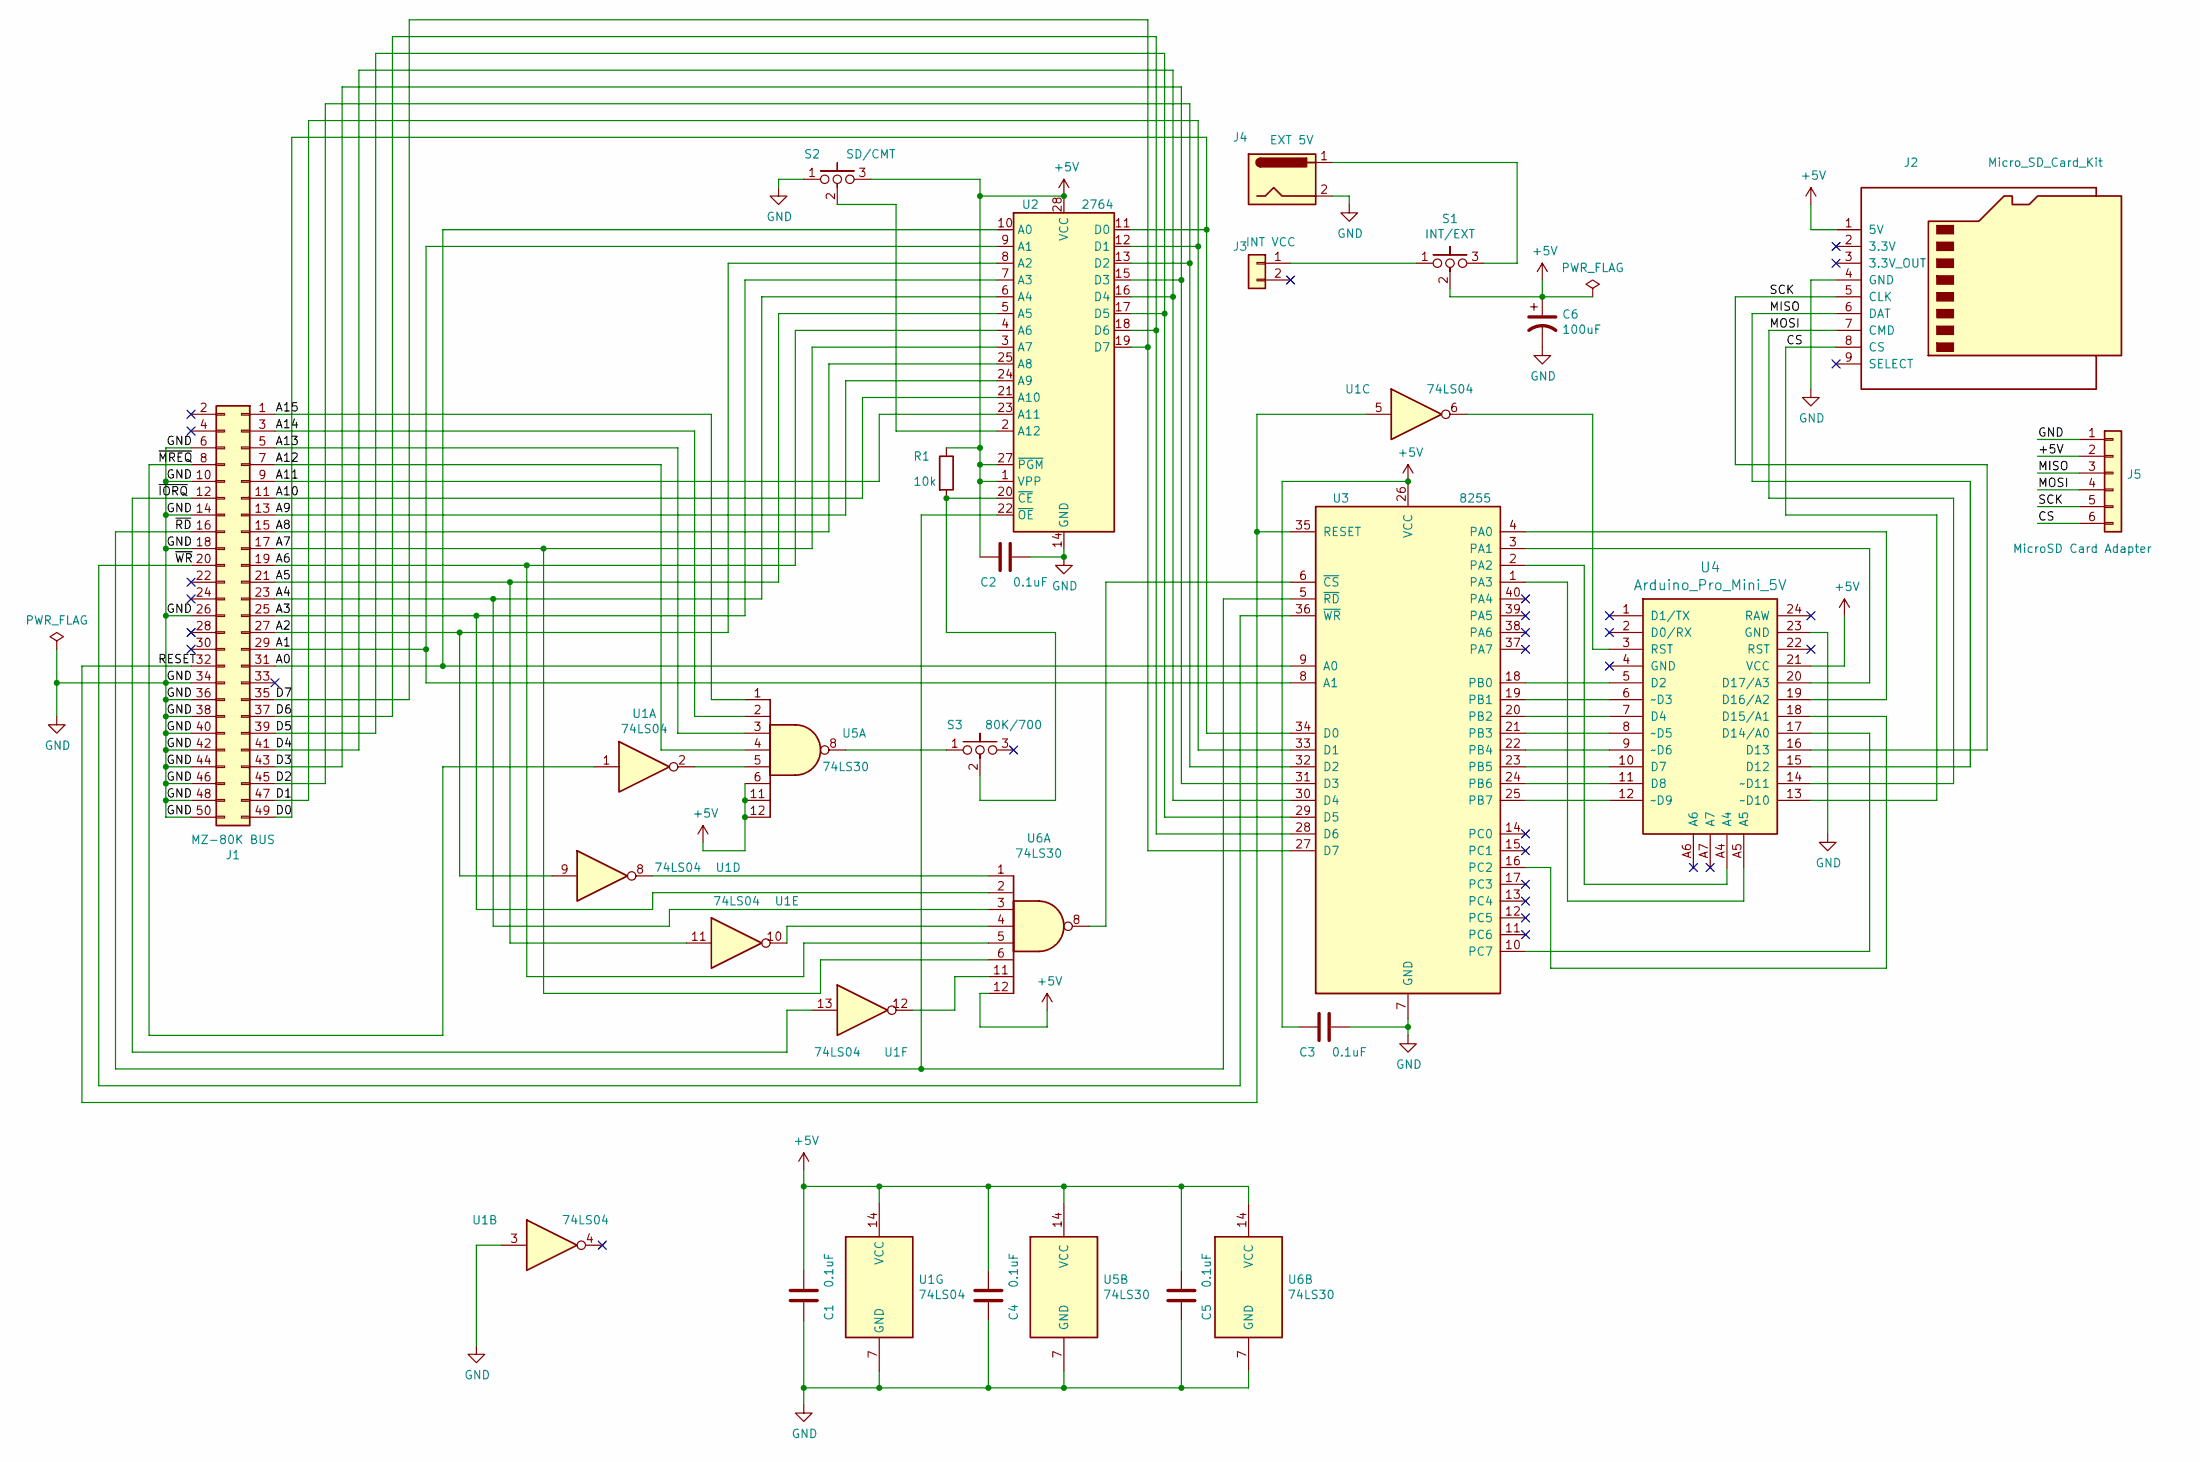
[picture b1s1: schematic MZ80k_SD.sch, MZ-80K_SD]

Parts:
C1, C2, C3, C4, C5: 0.1uF; C_Rect_L4.0mm_W2.5mm_P2.50mm
C6: 100uF; CP_Radial_D5.0mm_P2.50mm
J1: MZ-80K BUS; PinSocket_2x25_P2.54mm_Horizontal
J2: Micro_SD_Card_Kit; AE-microSD-LLCNV
J3: INT VCC; PinHeader_1x02_P2.54mm_Horizontal
J4: EXT 5V; BarrelJack_Horizontal
J5: MicroSD Card Adapter; PinSocket_1x06_P2.54mm_Vertical
R1: 10k; R_Axial_DIN0207_L6.3mm_D2.5mm_P7.62mm_Horizontal
S1: INT/EXT; PinHeader_1x03_P2.54mm_Vertical
S2: SD/CMT; PinHeader_1x03_P2.54mm_Vertical
S3: 80K/700; PinHeader_1x03_P2.54mm_Vertical
U1: 74LS04; DIP-14_W7.62mm_LongPads
U2: 2764; DIP-28_W15.24mm_LongPads
U3: 8255; DIP-40_W15.24mm_LongPads
U4: Arduino_Pro_Mini_5V; Arduino_Pro_Mini
U5, U6: 74LS30; DIP-14_W7.62mm_LongPads

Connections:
+5V: C1.2, C2.1, C3.1, C4.2, C5.2, C6.1, J2.1 (5V), J5.2, R1.1, S1.2, S2.3, U1.14 (VCC), U2.1 (VPP), U2.27 (~PGM), U2.28 (VCC), U3.26 (VCC), U4.21 (VCC), U5.6, U5.11, U5.12, U5.14 (VCC), U6.12, U6.14 (VCC)
/A0: J1.31, U2.10 (A0), U3.9 (A0)
/A1: J1.29, U2.9 (A1), U3.8 (A1)
/A2: J1.27, U1.9, U2.8 (A2)
/A3: J1.25, U2.7 (A3), U6.2
/A4: J1.23, U2.6 (A4), U6.3
/A5: J1.21, U1.11, U2.5 (A5)
/A6: J1.19, U2.4 (A6), U6.5
/A7: J1.17, U2.3 (A7), U6.6
/A8: J1.15, U2.25 (A8)
/A9: J1.13, U2.24 (A9)
/A10: J1.11, U2.21 (A10)
/A11: J1.9, U2.23 (A11)
/A12: J1.7, U5.4
/A13: J1.5, U5.3
/A14: J1.3, U5.2
/A15: J1.1, U5.1
/CS: J2.8 (CS), J5.6, U4.13 (~~D10)
/D0: J1.49, U2.11 (D0), U3.34 (D0)
/D1: J1.47, U2.12 (D1), U3.33 (D1)
/D2: J1.45, U2.13 (D2), U3.32 (D2)
/D3: J1.43, U2.15 (D3), U3.31 (D3)
/D4: J1.41, U2.16 (D4), U3.30 (D4)
/D5: J1.39, U2.17 (D5), U3.29 (D5)
/D6: J1.37, U2.18 (D6), U3.28 (D6)
/D7: J1.35, U2.19 (D7), U3.27 (D7)
/MISO: J2.6 (DAT), J5.3, U4.15 (D12)
/MOSI: J2.7 (CMD), J5.4, U4.14 (~~D11)
/RESET: J1.32, U1.5, U3.35 (RESET)
/SCK: J2.5 (CLK), J5.5, U4.16 (D13)
/~IORQ: J1.12, U1.13
/~MREQ: J1.8, U1.1
/~RD: J1.16, U2.22 (~OE), U3.5 (~RD~)
/~WR: J1.20, U3.36 (~WR~)
GND: C1.1, C2.2, C3.2, C4.1, C5.1, C6.2, J1.6, J1.10, J1.14, J1.18, J1.26, J1.34, J1.36, J1.38, J1.40, J1.42, J1.44, J1.46, J1.48, J1.50, J2.4 (GND), J4.2, J5.1, S2.1, U1.3, U1.7 (GND), U2.14 (GND), U3.7 (GND), U4.23 (GND), U5.7 (GND), U6.7 (GND)
unnamed: J3.1, S1.1
unnamed: J4.1, S1.3
unnamed: R1.2, S3.2, U2.20 (~CE)
unnamed: S2.2, U2.2 (A12)
unnamed: S3.1, U5.8
unnamed: U1.2, U5.5
unnamed: U1.6, U4.3 (RST)
unnamed: U1.8, U6.1
unnamed: U1.10, U6.4
unnamed: U1.12, U6.11
unnamed: U3.1 (PA3), U4.A5
unnamed: U3.2 (PA2), U4.A4
unnamed: U3.3 (PA1), U4.20 (D17/A3)
unnamed: U3.4 (PA0), U4.19 (D16/A2)
unnamed: U3.6 (~CS~), U6.8
unnamed: U3.10 (PC7), U4.17 (D14/A0)
unnamed: U3.16 (PC2), U4.18 (D15/A1)
unnamed: U3.18 (PB0), U4.5 (D2)
unnamed: U3.19 (PB1), U4.6 (~~D3)
unnamed: U3.20 (PB2), U4.7 (D4)
unnamed: U3.21 (PB3), U4.8 (~~D5)
unnamed: U3.22 (PB4), U4.9 (~~D6)
unnamed: U3.23 (PB5), U4.10 (D7)
unnamed: U3.24 (PB6), U4.11 (D8)
unnamed: U3.25 (PB7), U4.12 (~~D9)

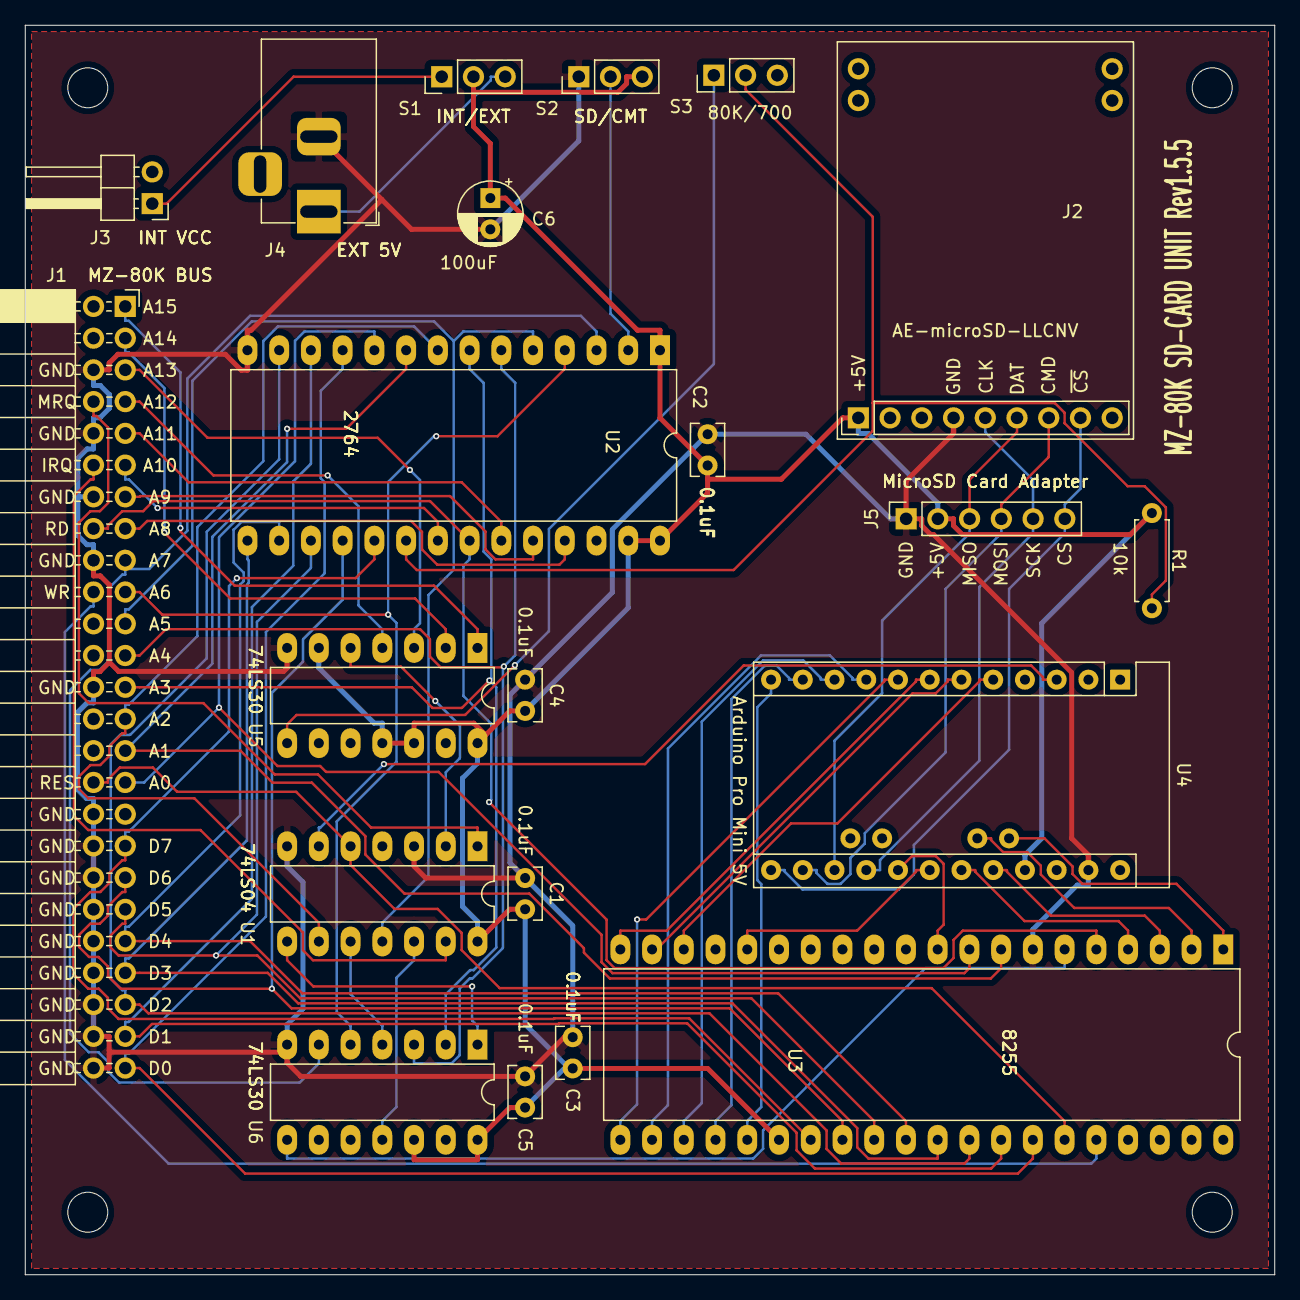
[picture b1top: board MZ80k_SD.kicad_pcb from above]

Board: 2 copper layers, 100.0 x 100.0 mm, 25 parts (0 on the bottom side), 60 nets.

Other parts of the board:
MH1, MH2, MH3, MH4: MountingHole_3.2mm_M3
